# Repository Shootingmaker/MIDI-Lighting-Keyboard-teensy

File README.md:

# MIDI-Lighting-Keyboard-teensy
This repository for like this video.
https://www.youtube.com/watch?v=D2VWIVyrJ5M&feature=youtu.be

[Library needs]

MIDI
https://github.com/FortySevenEffects/arduino_midi_library

MIDIcontoroller
https://github.com/joshnishikawa/MIDIcontroller

Teensyduino
https://www.pjrc.com/teensy/teensyduino.html

[Setting] 

board Teensy3.2

tool -> USB Type -> TeensyMIDI 

CPU:72Mhz

Faster with LTO

[Edit some libraly]

"MIDI.h" with MIDIcontoroller with TeensyMIDI

Change it

[midi_Settings.h]  

-> static const unsigned SysExMaxSize = 50000;

-> static const bool UseRunningStatus = true;

MIDIcontoroller

Change it

 [MIDIbutton.h]   - >#include "Flicker.h  =>  #include "Flicker/Flicker.h"

[Memo]
How to Using USB MIDI
https://www.pjrc.com/teensy/td_midi.html

[to LED(APA102) Wireing]
 5V & GND
 MOSI is  11
 CLK  is  13

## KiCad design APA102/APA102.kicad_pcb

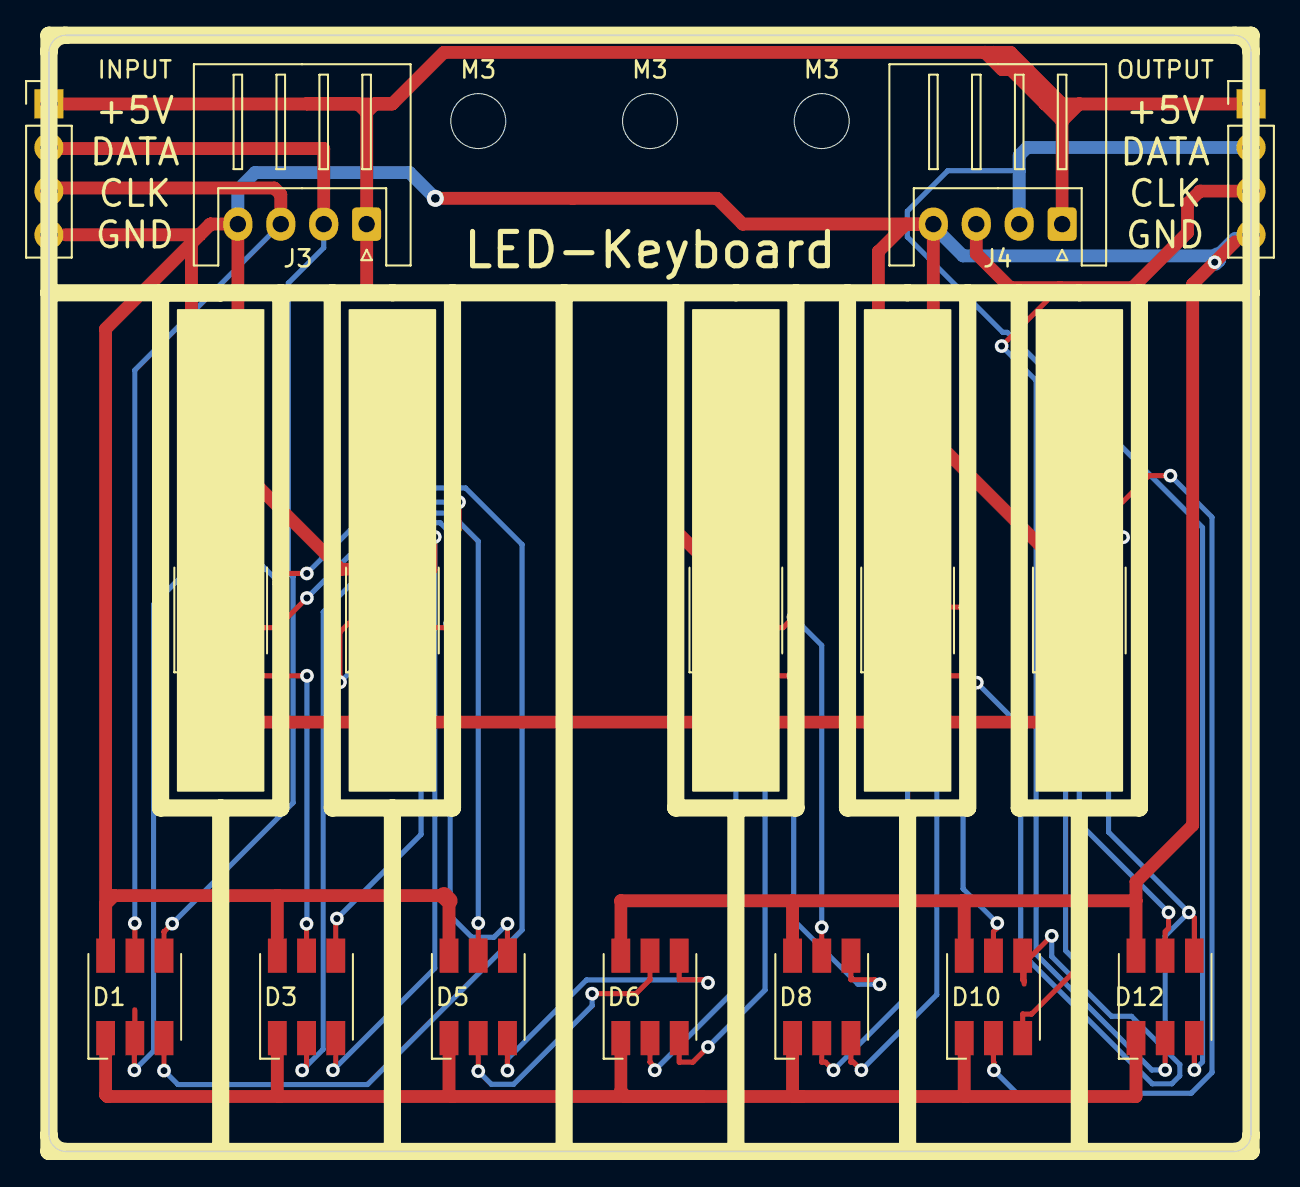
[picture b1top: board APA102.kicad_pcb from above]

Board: 2 copper layers, 70.0 x 65.0 mm, 19 parts (0 on the bottom side), 28 nets.

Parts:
D1, D2, D3, D4, D5, D6, D7, D8, D9, D10, D11, D12: APA102C; LED_RGB_5050-6
INPUT: Conn_01x04_Female; PinHeader_1x04_P2.54mm_Vertical
J3, J4: Conn_01x04_Male; JST_XH_S4B-XH-A_1x04_P2.50mm_Horizontal
M3, M3#2, M3#3: MountingHole_3.2mm_M3
OUTPUT: Conn_01x04_Female; PinHeader_1x04_P2.54mm_Vertical

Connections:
+5V: D1.1, D2.1, D3.1, D4.1, D5.1, D6.1, D7.1, D8.1, D9.1, D10.1, D11.1, D12.1, INPUT.1, J3.1, J4.1, OUTPUT.1
GND: D1.6, D2.6, D3.6, D4.6, D5.6, D6.6, D7.6, D8.6, D9.6, D10.6, D11.6, D12.6, INPUT.4, J3.4, J4.4, OUTPUT.4
unnamed: D1.2, D2.5
unnamed: D1.3, D2.4
unnamed: D1.4, INPUT.2, J3.2
unnamed: D1.5, INPUT.3, J3.3
unnamed: D2.2, D3.5
unnamed: D2.3, D3.4
unnamed: D3.2, D4.5
unnamed: D3.3, D4.4
unnamed: D4.2, D5.5
unnamed: D4.3, D5.4
unnamed: D5.2, D6.5
unnamed: D5.3, D6.4
unnamed: D6.2, D7.5
unnamed: D6.3, D7.4
unnamed: D7.2, D8.5
unnamed: D7.3, D8.4
unnamed: D8.2, D9.5
unnamed: D8.3, D9.4
unnamed: D10.2, D11.5
unnamed: D10.3, D11.4
unnamed: D9.3, D10.4
unnamed: D9.2, D10.5
unnamed: D11.2, D12.5
unnamed: D11.3, D12.4
unnamed: D12.2, J4.3, OUTPUT.3
unnamed: D12.3, J4.2, OUTPUT.2

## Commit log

2019-03-13 First upload.
    it works.
2019-04-29 Stable Version
    Teensy3.2
    72Mhz
    USB-MIDI
2019-05-19 Hardware add
2020-06-28 Add 88LED/Teensy4.0
